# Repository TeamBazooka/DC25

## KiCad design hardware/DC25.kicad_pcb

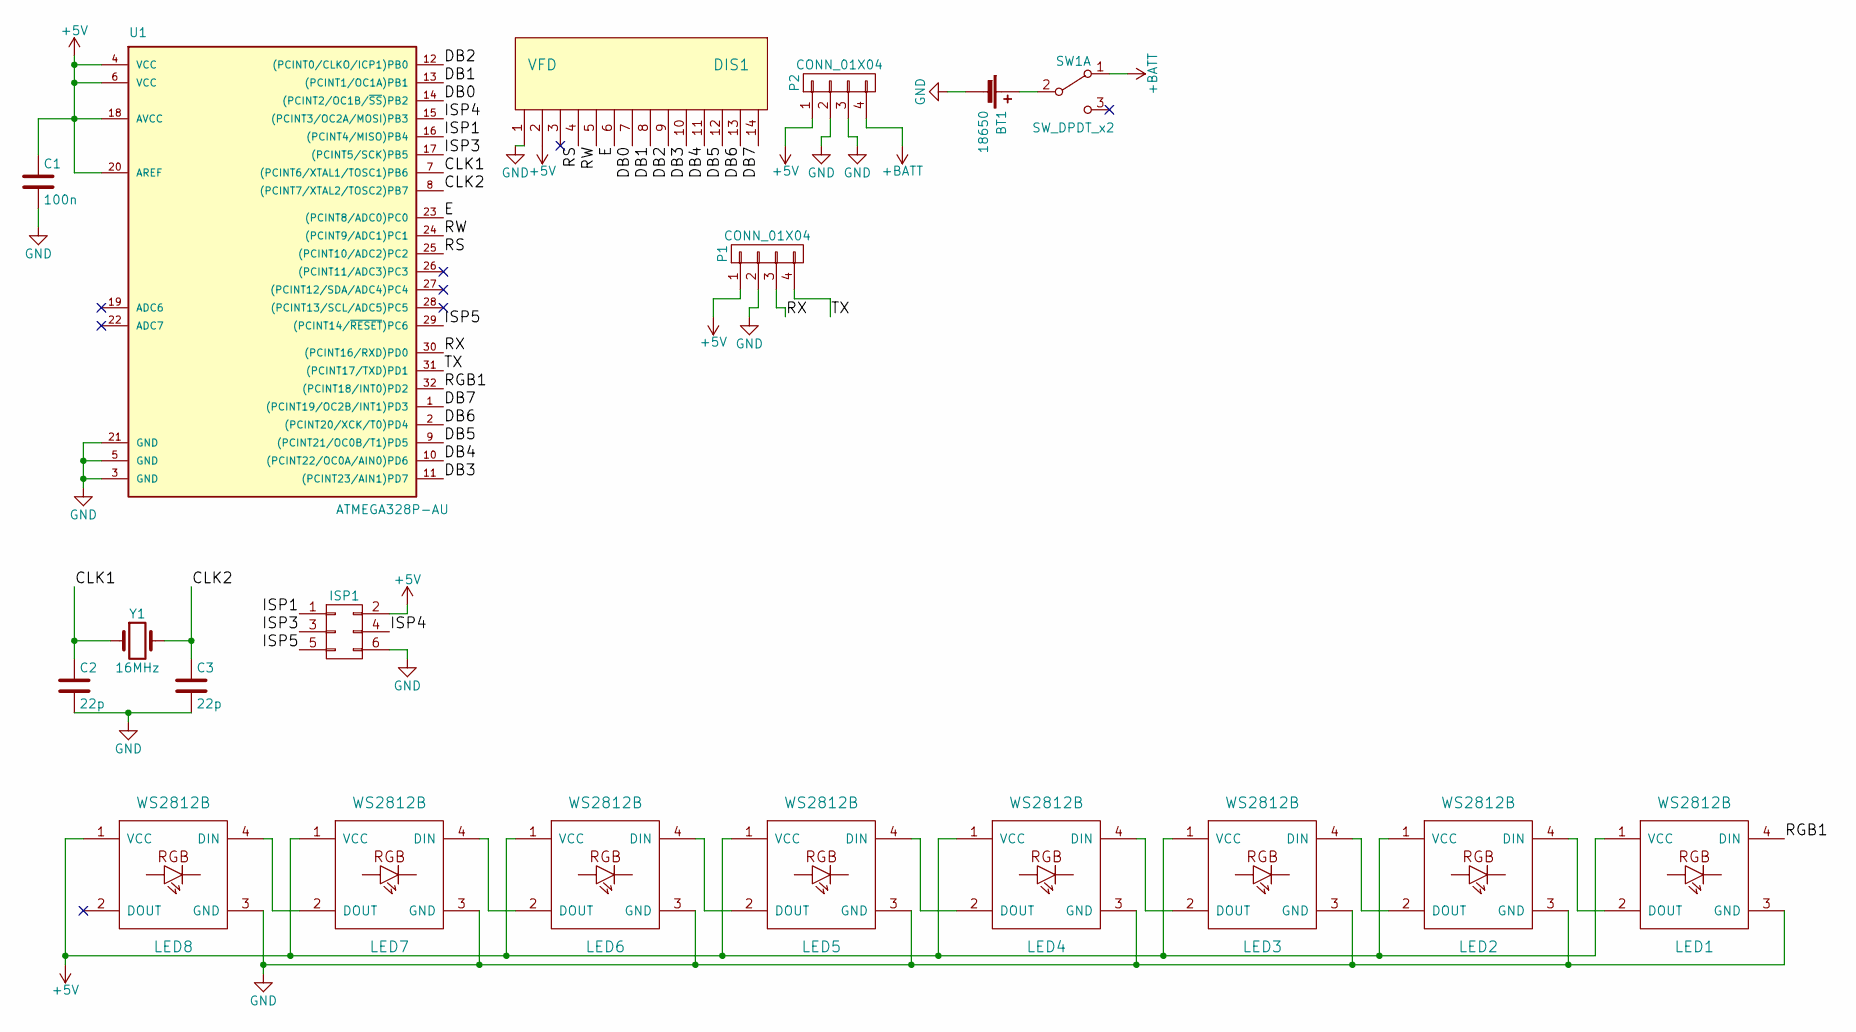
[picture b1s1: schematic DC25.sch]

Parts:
BT1: 18650; Pin_Header_Straight_1x02_Pitch2.54mm
C1: 100n; C_0603_HandSoldering
C2, C3: 22p; C_0603_HandSoldering
DIS1: VFD
ISP1: CONN_02X03; Pin_Header_Straight_2x03_Pitch2.54mm
LED1, LED2, LED3, LED4, LED5, LED6, LED7, LED8: WS2812B
P1, P2: CONN_01X04; Pin_Header_Straight_1x04_Pitch2.54mm
SW1: SW_DPDT_x2; switch_EG2219
U1: ATMEGA328P-AU; TQFP-32_7x7mm_Pitch0.8mm
Y1: 16MHz; Crystal_SMD_HC49-SD_HandSoldering

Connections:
+5V: C1.1, DIS1.2, ISP1.2, LED1.1 (VCC), LED2.1 (VCC), LED3.1 (VCC), LED4.1 (VCC), LED5.1 (VCC), LED6.1 (VCC), LED7.1 (VCC), LED8.1 (VCC), P1.1, P2.1, U1.4 (VCC), U1.6 (VCC), U1.18 (AVCC), U1.20 (AREF)
+BATT: P2.4, SW1.1 (A)
/CLK1: C2.1, U1.7 ((PCINT6/XTAL1/TOSC1)PB6), Y1.1
/CLK2: C3.1, U1.8 ((PCINT7/XTAL2/TOSC2)PB7), Y1.2
/DB0: DIS1.7, U1.14 ((PCINT2/OC1B/~SS~)PB2)
/DB1: DIS1.8, U1.13 ((PCINT1/OC1A)PB1)
/DB2: DIS1.9, U1.12 ((PCINT0/CLKO/ICP1)PB0)
/DB3: DIS1.10, U1.11 ((PCINT23/AIN1)PD7)
/DB4: DIS1.11, U1.10 ((PCINT22/OC0A/AIN0)PD6)
/DB5: DIS1.12, U1.9 ((PCINT21/OC0B/T1)PD5)
/DB6: DIS1.13, U1.2 ((PCINT20/XCK/T0)PD4)
/DB7: DIS1.14, U1.1 ((PCINT19/OC2B/INT1)PD3)
/E: DIS1.6, U1.23 ((PCINT8/ADC0)PC0)
/ISP1: ISP1.1, U1.16 ((PCINT4/MISO)PB4)
/ISP3: ISP1.3, U1.17 ((PCINT5/SCK)PB5)
/ISP4: ISP1.4, U1.15 ((PCINT3/OC2A/MOSI)PB3)
/ISP5: ISP1.5, U1.29 ((PCINT14/~RESET~)PC6)
/RGB1: LED1.4 (DIN), U1.32 ((PCINT18/INT0)PD2)
/RS: DIS1.4, U1.25 ((PCINT10/ADC2)PC2)
/RW: DIS1.5, U1.24 ((PCINT9/ADC1)PC1)
/RX: P1.3, U1.30 ((PCINT16/RXD)PD0)
/TX: P1.4, U1.31 ((PCINT17/TXD)PD1)
GND: BT1.2 (-), C1.2, C2.2, C3.2, DIS1.1, ISP1.6, LED1.3 (GND), LED2.3 (GND), LED3.3 (GND), LED4.3 (GND), LED5.3 (GND), LED6.3 (GND), LED7.3 (GND), LED8.3 (GND), P1.2, P2.2, P2.3, U1.3 (GND), U1.5 (GND), U1.21 (GND)
unnamed: BT1.1 (+), SW1.2 (B)
unnamed: LED1.2 (DOUT), LED2.4 (DIN)
unnamed: LED2.2 (DOUT), LED3.4 (DIN)
unnamed: LED3.2 (DOUT), LED4.4 (DIN)
unnamed: LED4.2 (DOUT), LED5.4 (DIN)
unnamed: LED5.2 (DOUT), LED6.4 (DIN)
unnamed: LED6.2 (DOUT), LED7.4 (DIN)
unnamed: LED7.2 (DOUT), LED8.4 (DIN)

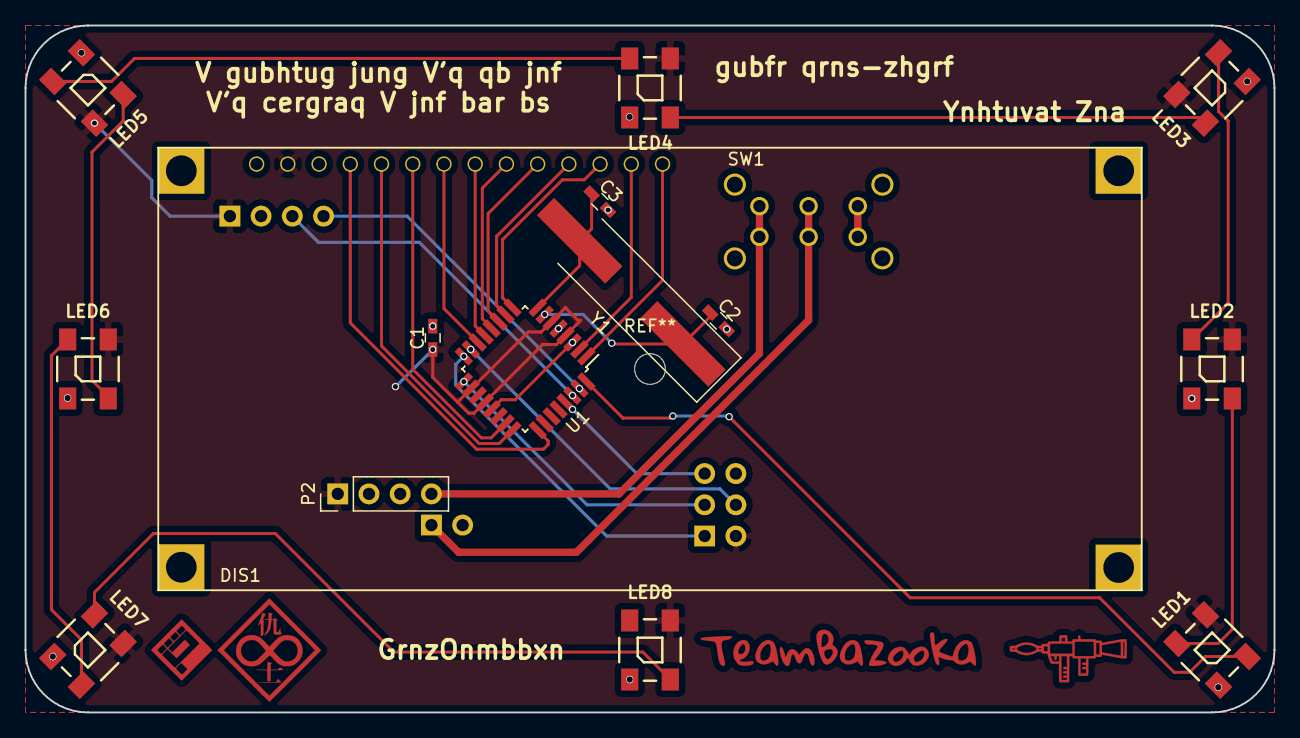
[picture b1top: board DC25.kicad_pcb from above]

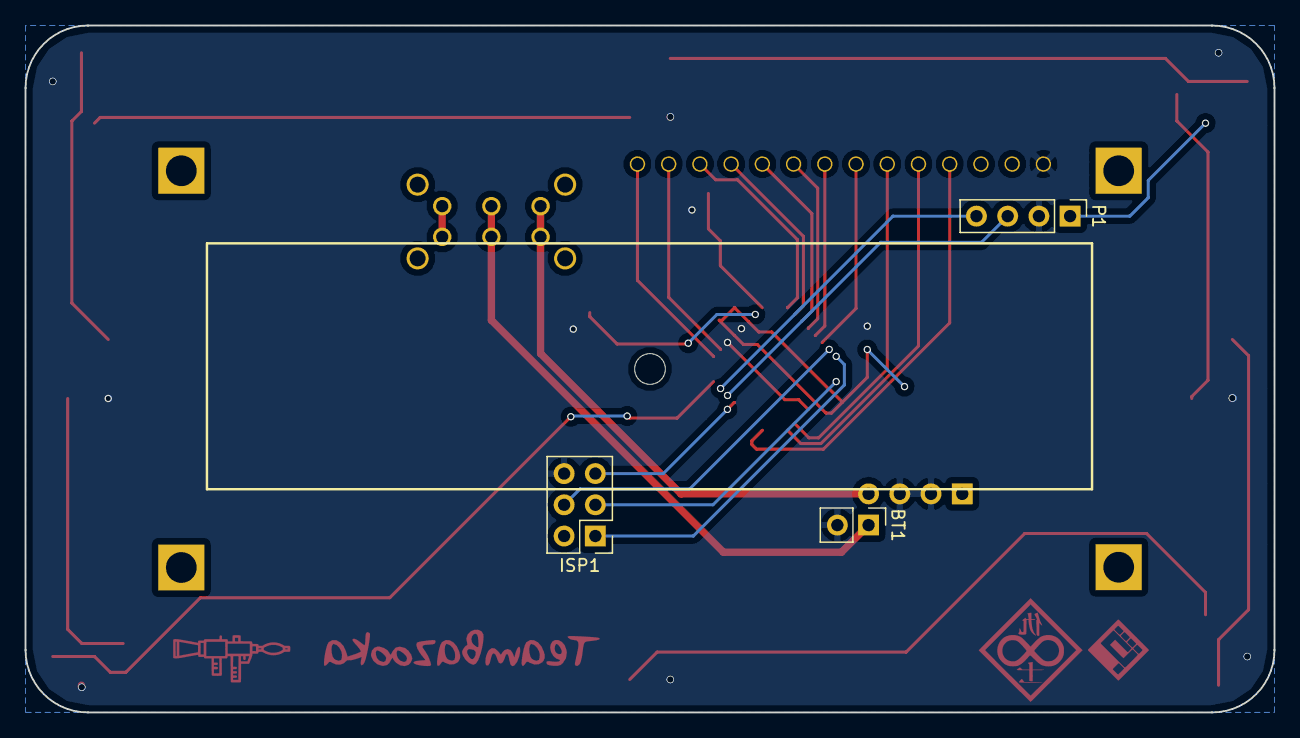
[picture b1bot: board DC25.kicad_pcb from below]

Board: 2 copper layers, 101.6 x 55.9 mm, 19 parts (3 on the bottom side), 31 nets.

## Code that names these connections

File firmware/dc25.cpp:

#define NEED_CXX_BITS
#include <Adafruit_NeoPixel.h>
#include <LiquidCrystal.h>

#include "strings.h"
#include "line_info.h"
#include "RgbAnimations.h"

#define SIZECHAR 1

#define COLUMNS 16
#define ROWS 2
#define LCD_DELAY 250

#define RANDOM random(0, STR_COUNT)
#define RANDOM_STOP random(4, 9)

#define RGB_LED_PIN PD2
#define RGB_LED_COUNT 8

LiquidCrystal *lcd;

Adafruit_NeoPixel *leds;

LineInfo *lineOne;
LineInfo *lineTwo;

RgbAnimations *animations;
unsigned int rgbDelay = 50;
unsigned long last_time_lcd;
unsigned long last_time_rgb;

void setup() {
  randomSeed(0xCAFEF00D);
  //                       RS,  RW,   E,  D0,  D1,  D2, D3, D4, D5, D6, D7
  lcd = new LiquidCrystal(PC2, PC1, PC0, PB2, PB1, PB0, PD7, PD6, PD5, PD4, PD3);
  //lcd = new LiquidCrystal(2,  3, 4,  5,  6,  7,  8,  9, 10, 11, 12);
  // set up the LCD's number of columns and rows:
  lcd->begin(COLUMNS, ROWS);

  lineOne = liInit(COLUMNS, SIZECHAR, RANDOM);
  lineTwo = liInit(COLUMNS, SIZECHAR, RANDOM);
  while(lineOne->str == lineTwo->str) {
    lineTwo->str = RANDOM;
  }
  lineTwo->stop = RANDOM_STOP;

  leds = new Adafruit_NeoPixel(RGB_LED_COUNT, RGB_LED_PIN, NEO_GRB + NEO_KHZ800);

  animations = new RgbAnimations(leds, RGB_LED_COUNT);
  animations->selectAnimation();

  last_time_lcd = millis();
  last_time_rgb = millis();
}

void incrementLine(LineInfo *currentLine, LineInfo *prevLine) {
  char thisChar;
  if(currentLine->stop != 0) {
    currentLine->stop--;
    cbPush(currentLine->cb);
  } else {
    memcpy_P(&thisChar, strings[currentLine->str] + (currentLine->ch * SIZECHAR), SIZECHAR);
    if(thisChar != '\0') {
      cbPush(currentLine->cb, &thisChar);
      currentLine->ch++;
    } else {
      currentLine->str = RANDOM;
      while(currentLine->str == prevLine->str) {
        currentLine->str = RANDOM;
      }
      currentLine->stop = RANDOM_STOP;
      currentLine->ch = 0;
      cbPush(currentLine->cb);
    }
  }
}

void writeToLcd() {
  incrementLine(lineOne, lineTwo);
  incrementLine(lineTwo, lineOne);

  char *currentColOne = lineOne->cb->head;
  char *currentColTwo = lineTwo->cb->head;
  for(int ii = 0; ii<COLUMNS;ii++) {
    lcd->setCursor(ii, 0);
    lcd->write(*currentColOne);
    lcd->setCursor(ii, 1);
    lcd->write(*currentColTwo);
    currentColOne = (char*) currentColOne + lineOne->cb->sz;
    currentColTwo = (char*) currentColTwo + lineTwo->cb->sz;
    if(currentColOne == lineOne->cb->bufferEnd) {
      currentColOne = lineOne->cb->buffer;
    }
    if(currentColTwo == lineTwo->cb->bufferEnd) {
      currentColTwo = lineTwo->cb->buffer;
    }
  }
}

void loop() {
  unsigned long now = millis();
  if ((now - last_time_lcd) >= LCD_DELAY) {
    //writeToLcd();
    last_time_lcd = now;
  }
  if ((now - last_time_rgb) >= rgbDelay) {
    bool select = animations->run();
    if(select) {
      rgbDelay = random(50, 250);
    }
    last_time_rgb = now;
  }
}

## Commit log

2017-03-22 move string count to strings.h
2017-03-22 remove some bad chars
2017-03-24 Some progress
2017-03-24 Some branding improvements
2017-03-24 More branding and RGB signal, gnd lines.
2017-03-24 remove plot files
2017-03-24 add gitignore
2017-03-25 Some firmware refactoring.
2017-03-25 Get rid of bak files.
2017-03-25 Finish board layout.
2017-03-26 Some more firmware refactoring
2017-03-26 remove ground via, put swith on battery positive sideq
2017-03-26 More refactoring
2017-03-26 more strings
2017-03-26 add battery holder mounting hole
2017-04-01 Use cmake to build firmware
2017-04-01 pipeline
2017-04-03 mode batter mounting down one notch
2017-04-08 add LiquidCrystal lib submodule
2017-04-08 remove neopixel lib
2017-04-08 add new pixel lib as submodule
2017-04-08 decrease build time
2017-04-08 remove display lib
2017-05-04 add some rgb led animations
2017-05-13 switch to platformio for build
2017-05-13 remove modules file
2017-05-14 it works!
2017-05-14 refactor lcd handling to its own class
2017-05-14 migrate to class based time keeping
2017-07-25 add some more animations
2017-07-26 Sleeping now works!
2017-07-26 fixup some of the randomness
